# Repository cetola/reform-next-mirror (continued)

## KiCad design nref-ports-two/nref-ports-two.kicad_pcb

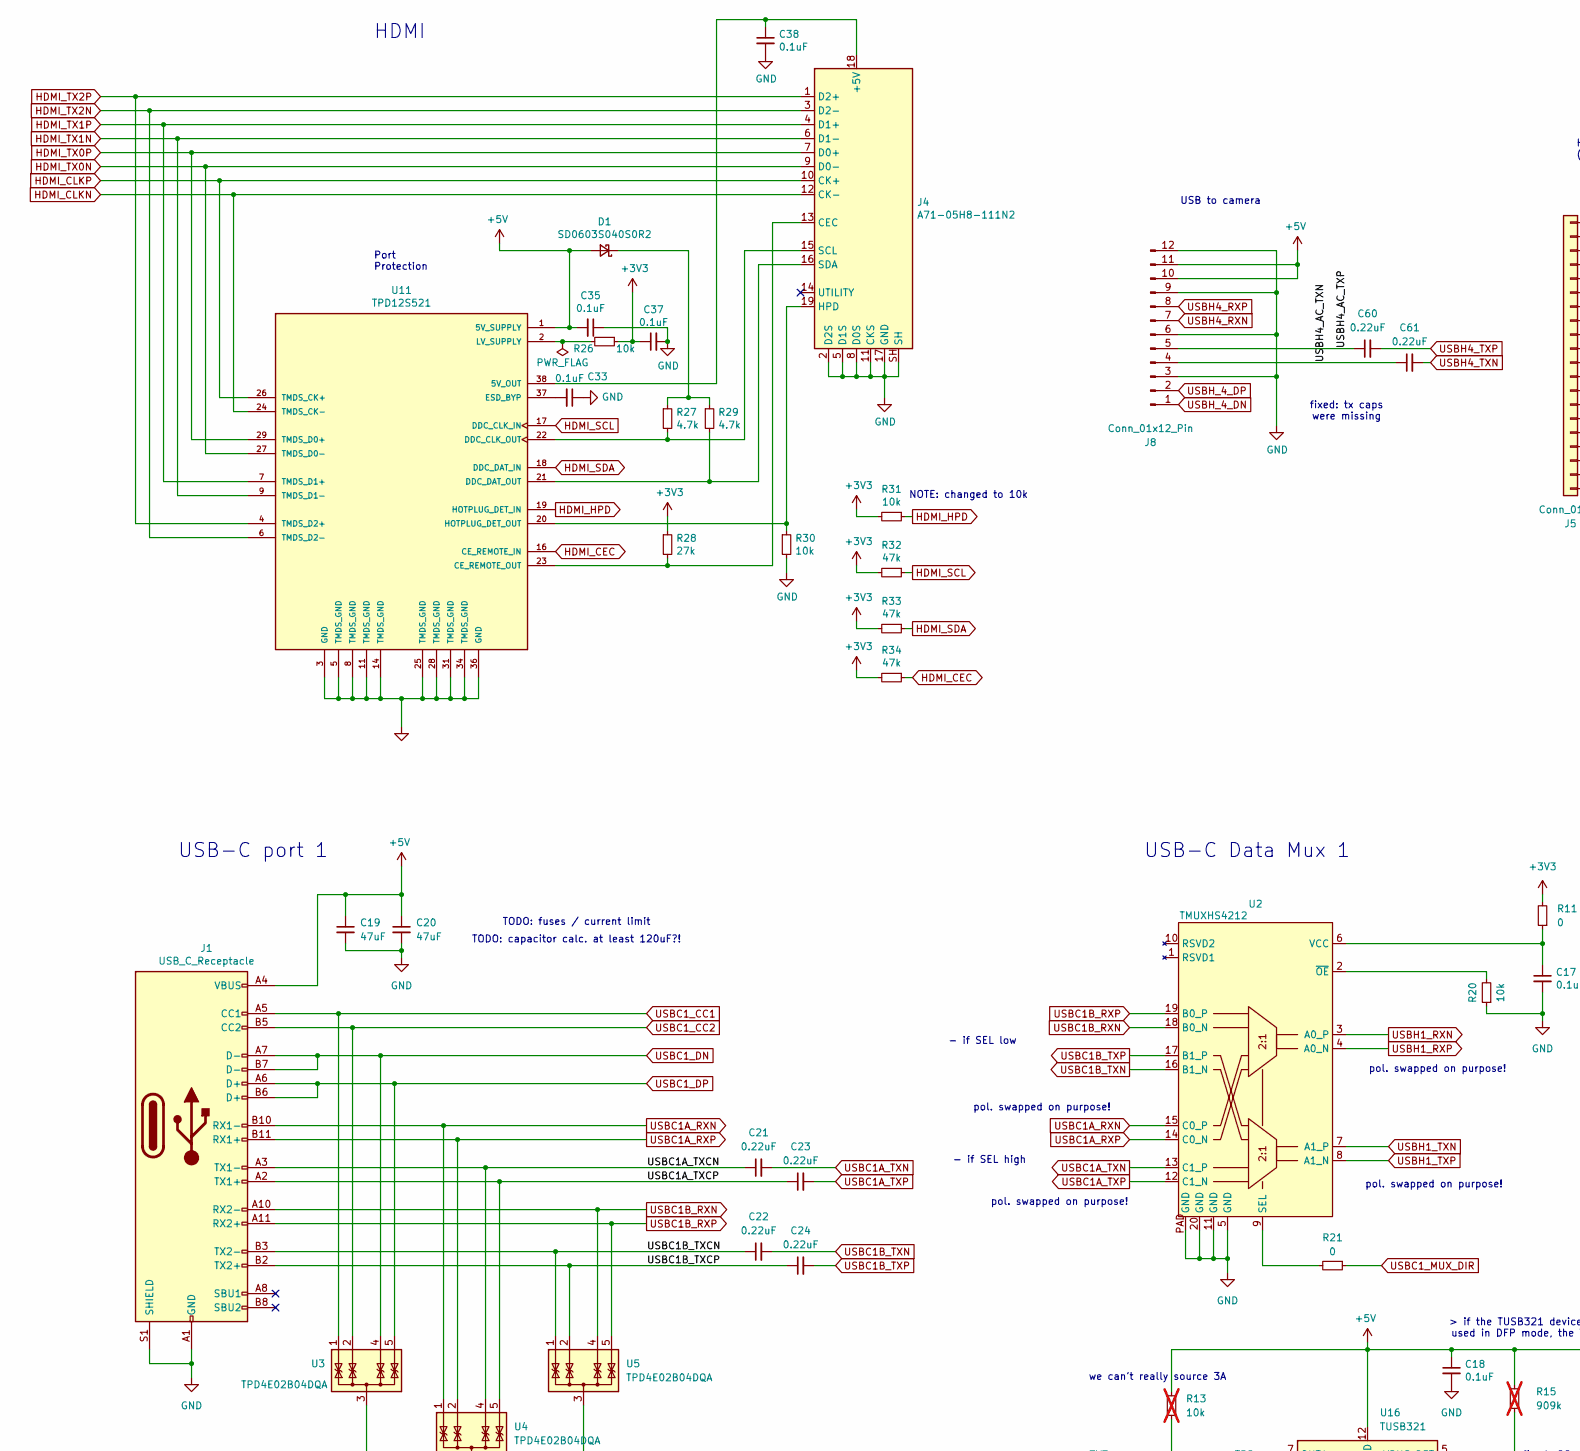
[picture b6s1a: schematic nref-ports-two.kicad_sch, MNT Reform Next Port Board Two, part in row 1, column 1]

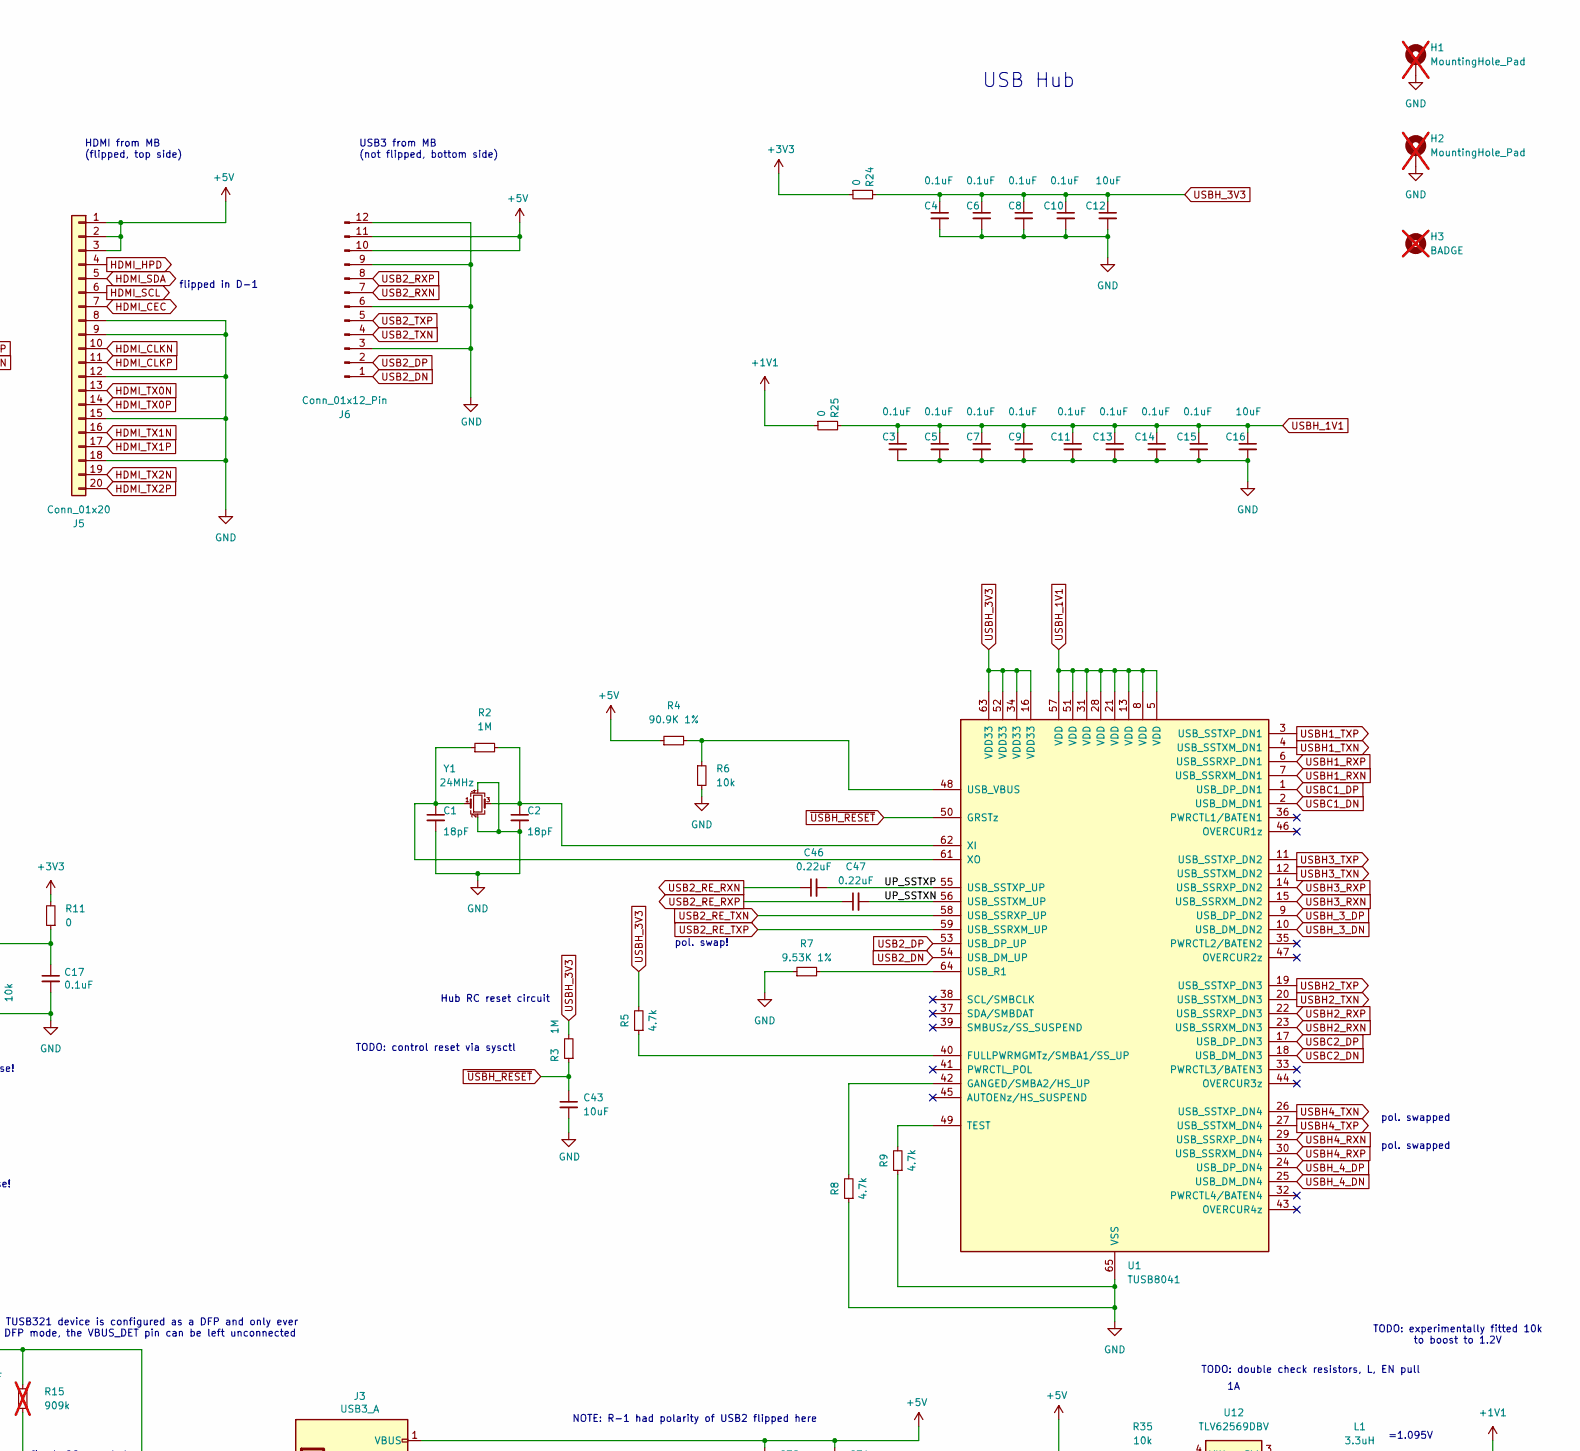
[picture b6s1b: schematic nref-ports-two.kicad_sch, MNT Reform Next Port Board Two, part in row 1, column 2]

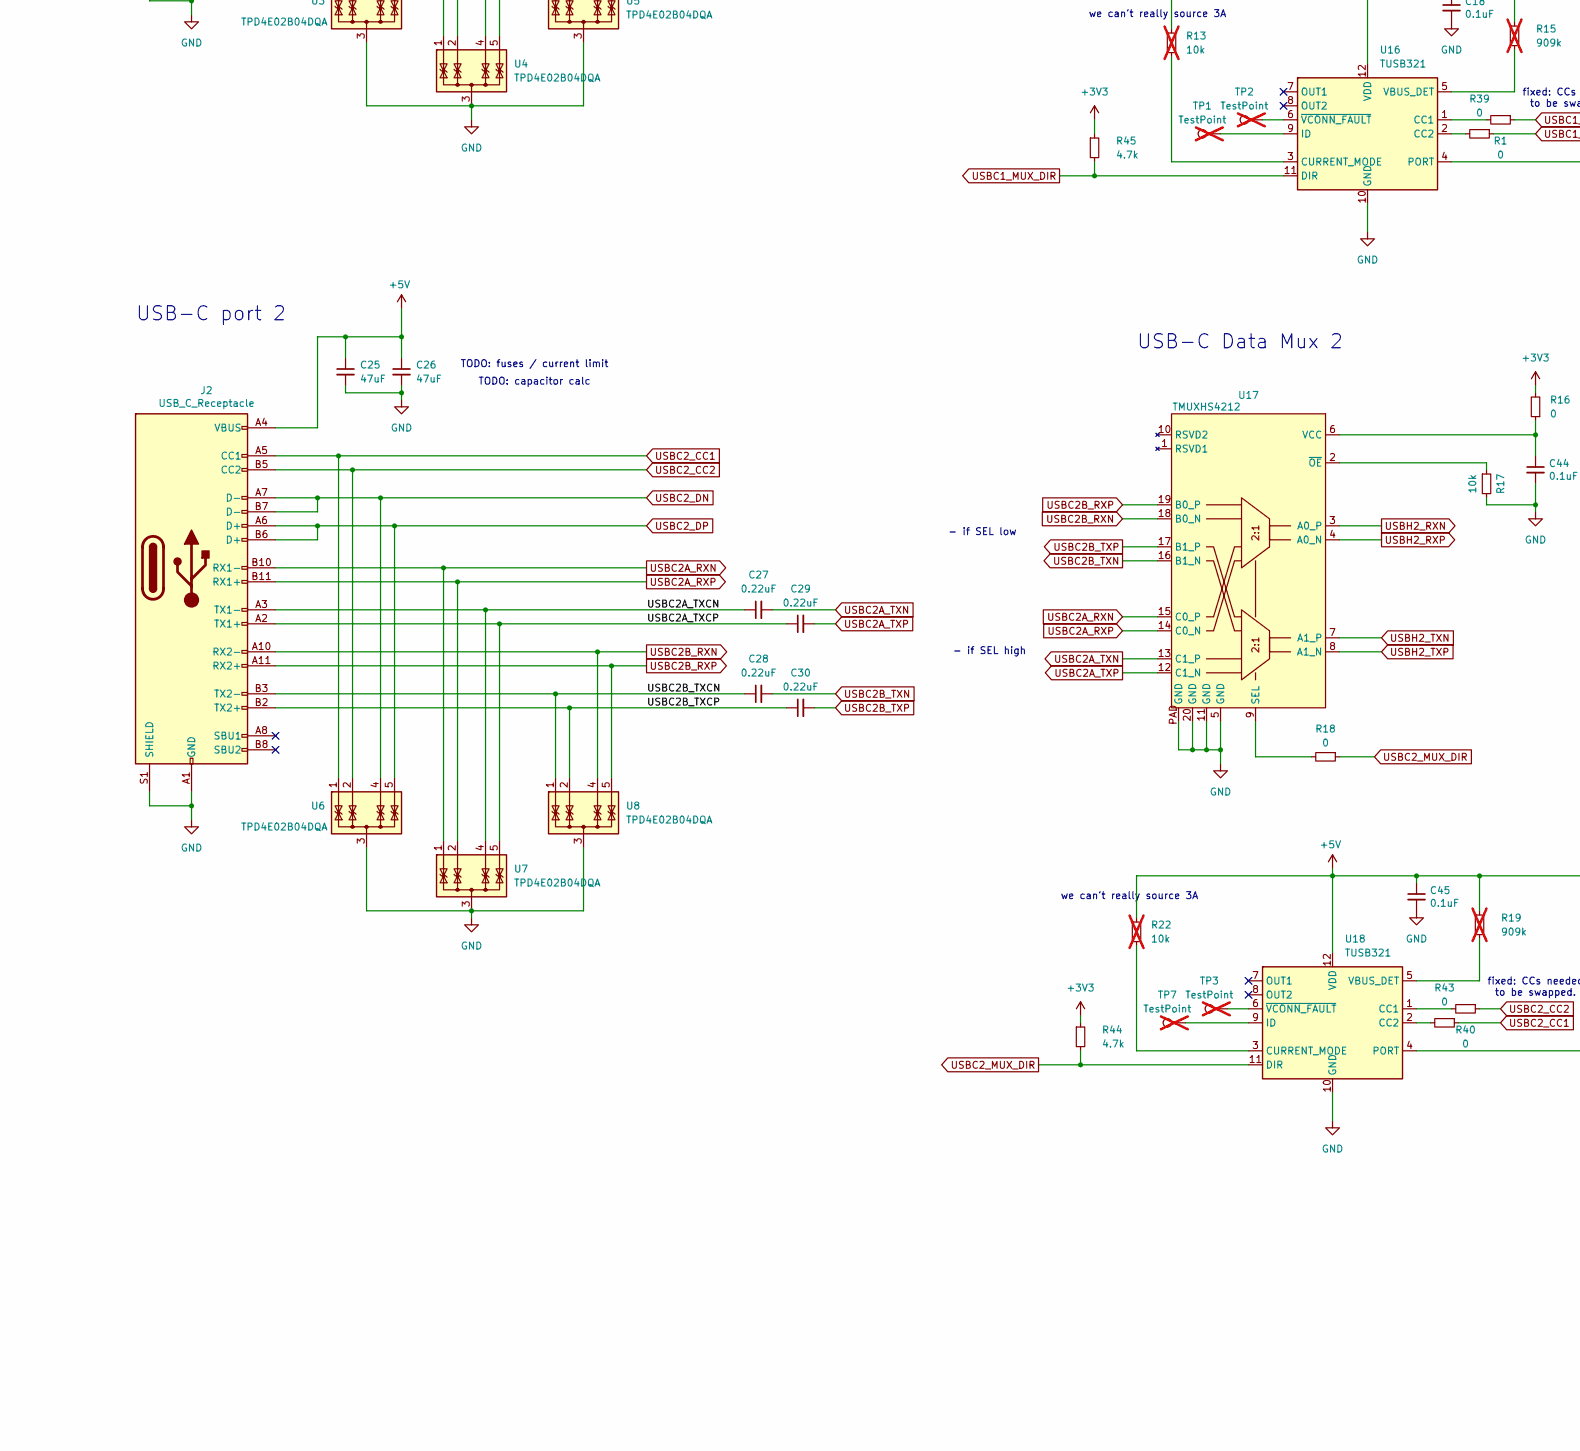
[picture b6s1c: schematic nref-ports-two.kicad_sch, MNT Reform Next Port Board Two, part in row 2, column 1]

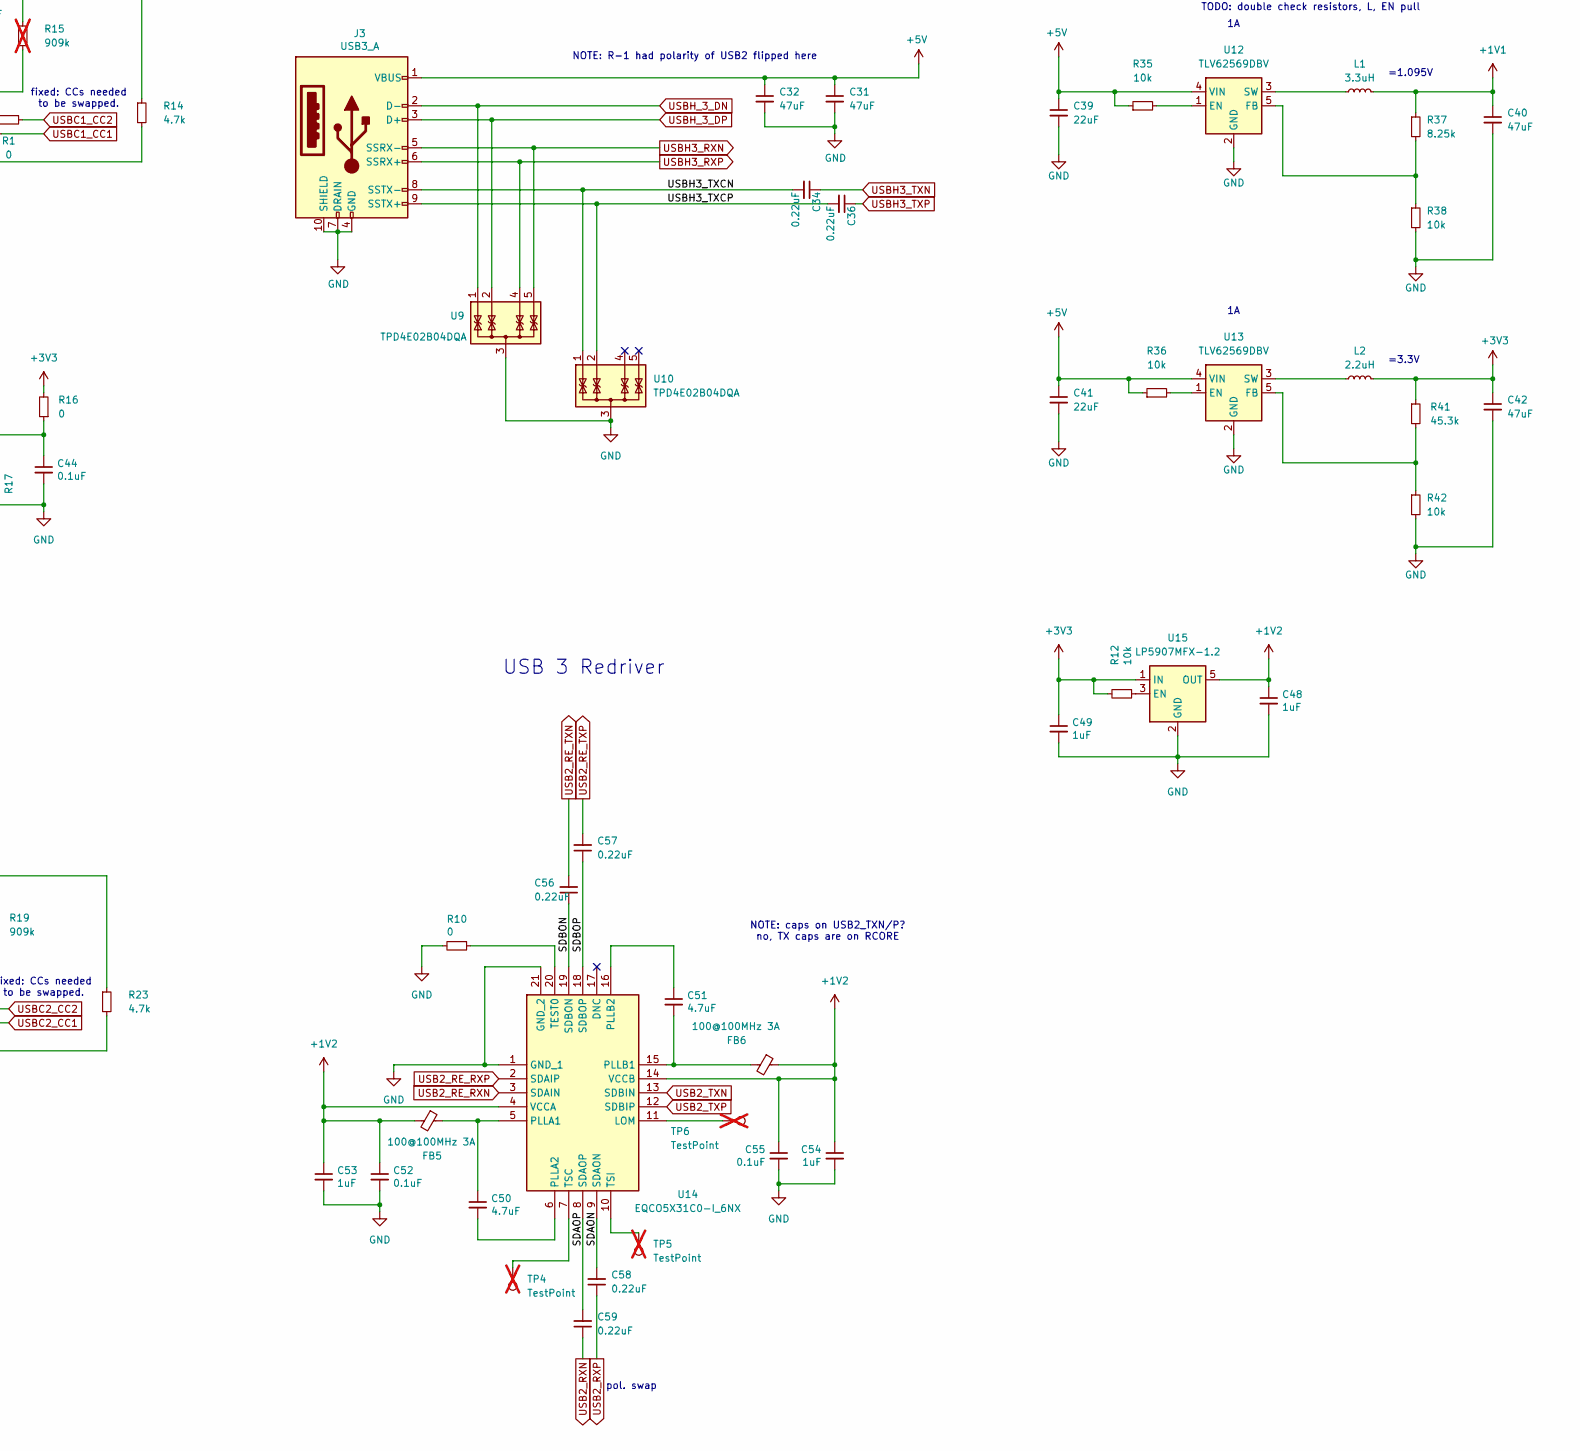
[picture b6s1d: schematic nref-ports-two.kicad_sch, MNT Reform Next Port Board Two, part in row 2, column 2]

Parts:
C1, C2: 18pF; C_0402_1005Metric; LCSC C1549
C3, C4, C5, C6, C7, C8, C9, C10, C11, C13, C14, C15, C17, C18, C33, C35, C37, C38, C44, C45, C52, C55: 0.1uF; C_0402_1005Metric; LCSC C1525
C12, C16, C43: 10uF; C_0603_1608Metric; LCSC C96446
C19, C20, C25, C26, C31, C32, C40, C42: 47uF; C_1206_3216Metric; LCSC C96123
C21, C22, C23, C24, C27, C28, C29, C30, C34, C36, C46, C47, C56, C57, C58, C59, C60, C61: 0.22uF; C_0402_1005Metric; LCSC C16772
C39, C41: 22uF; C_0603_1608Metric; LCSC C59461
C48, C49, C53, C54: 1uF; C_0402_1005Metric; LCSC C52923
C50, C51: 4.7uF; C_0402_1005Metric; LCSC C23733
D1: SD0603S040S0R2; D_0603_1608Metric; LCSC C143772
FB5, FB6: 100@100MHz 3A; L_0402_1005Metric; LCSC C124089
H1, H2: MountingHole_Pad; MountingHole_2.2mm_M2_Pad; not fitted
H3: BADGE; nref-ports-two-badge; not fitted
J1, J2: USB_C_Receptacle; USB_C_Receptacle_Molex_105450-0101; LCSC C134092
J3: USB3_A; USB-A-SMD_HC-USB3.0-C225-P; LCSC C7501855
J4: A71-05H8-111N2; HDMI-TH_A71-05H8-111N2; LCSC C2880638
J5: Conn_01x20; FPC-SMD_AFC07-S20ECC-00; LCSC C11090
J6, J8: Conn_01x12_Pin; Hirose_FH12-12S-0.5SH_1x12-1MP_P0.50mm_Horizontal; LCSC C262661
L1: 3.3uH; L_1210_3225Metric; LCSC C29780744
L2: 2.2uH; L_1210_3225Metric; LCSC C5832378
R1, R10, R11, R16, R18, R21, R24, R25, R39, R40, R43: 0; R_0402_1005Metric; LCSC C17168
R2, R3: 1M; R_0402_1005Metric; LCSC C26083
R4: 90.9K 1%; R_0402_1005Metric; LCSC C163452
R5, R8, R9, R14, R23, R27, R29, R44, R45: 4.7k; R_0402_1005Metric; LCSC C25900
R6, R12, R17, R20, R26, R30, R31, R35, R36, R38, R42: 10k; R_0402_1005Metric; LCSC C25744
R7: 9.53K 1%; R_0402_1005Metric; LCSC C96273
R13, R22: 10k; R_0402_1005Metric; LCSC C25744; not fitted
R15, R19: 909k; R_0402_1005Metric; LCSC C25799; not fitted
R28: 27k; R_0402_1005Metric; LCSC C25771
R32, R33, R34: 47k; R_0402_1005Metric; LCSC C25792
R37: 8.25k; R_0402_1005Metric; LCSC C5126132
R41: 45.3k; R_0402_1005Metric; LCSC C2933099
TP1, TP2, TP3, TP4, TP5, TP6, TP7: TestPoint; TestPoint_Pad_D1.0mm; not fitted
U1: TUSB8041; QFN-64-1EP_9x9mm_P0.5mm_EP6x6mm_ThermalVias; LCSC C544686
U2, U17: TMUXHS4212; Texas-VQFN20_2.5x4.5mm_RKS; LCSC C2869871
U3, U4, U5, U6, U7, U8, U9, U10: TPD4E02B04DQA; USON-10_2.5x1.0mm_P0.5mm; LCSC C2841426
U11: TPD12S521; TSSOP50P640X120-38N; LCSC C126920
U12, U13: TLV62569DBV; SOT-23-5; LCSC C141836
U14: EQCO5X31C0-I_6NX; QFN50P400X400X100-21N-D; LCSC C19729370
U15: LP5907MFX-1.2; SOT-23-5; LCSC C73478
U16, U18: TUSB321; Texas_X2QFN-12_1.6x1.6mm_P0.4mm; LCSC C2674046
Y1: 24MHz; Crystal_SMD_Abracon_ABM8G-4Pin_3.2x2.5mm; LCSC C91744

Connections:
+1V1: C40.1, L1.2, R25.1, R37.1
+1V2: C48.1, C52.1, C53.1, C54.1, C55.1, FB5.2, FB6.1, U14.4 (VCCA), U14.14 (VCCB), U15.5 (OUT)
+3V3: C37.1, C42.1, C49.1, L2.2, R11.2, R12.2, R16.2, R24.1, R26.1, R28.1, R31.2, R32.2, R33.2, R34.2, R41.1, R44.1, R45.1, U15.1 (IN)
+5V: C18.1, C19.1, C20.1, C25.1, C26.1, C31.1, C32.1, C35.2, C39.1, C41.1, C45.1, D1.2 (A), J1.A4 (VBUS), J1.A9 (VBUS), J1.B4 (VBUS), J1.B9 (VBUS), J2.A4 (VBUS), J2.A9 (VBUS), J2.B4 (VBUS), J2.B9 (VBUS), J3.1 (VBUS), J5.1, J5.2, J5.3, J6.10, J6.11, J8.10, J8.11, R4.1, R13.1, R14.1, R15.1, R19.1, R22.1, R23.1, R35.1, R36.1, U11.1 (5V_SUPPLY), U12.4 (VIN), U13.4 (VIN), U16.12 (VDD), U18.12 (VDD)
/SDAON: C58.2, U14.9 (SDAON)
/SDAOP: C59.2, U14.8 (SDAOP)
/SDBON: C56.1, U14.19 (SDBON)
/SDBOP: C57.1, U14.18 (SDBOP)
/UP_SSTXN: C47.2, U1.56 (USB_SSTXM_UP)
/UP_SSTXP: C46.2, U1.55 (USB_SSTXP_UP)
/USBC1A_TXCN: C21.1, J1.A3 (TX1-), U4.4 (IO3), U4.7 (IO3)
/USBC1A_TXCP: C23.1, J1.A2 (TX1+), U4.5 (IO4), U4.6 (IO4)
/USBC1B_TXCN: C22.1, J1.B3 (TX2-), U5.1 (IO1), U5.10 (IO1)
/USBC1B_TXCP: C24.1, J1.B2 (TX2+), U5.2 (IO2), U5.9 (IO2)
/USBC2A_TXCN: C27.1, J2.A3 (TX1-), U7.4 (IO3), U7.7 (IO3)
/USBC2A_TXCP: C29.1, J2.A2 (TX1+), U7.5 (IO4), U7.6 (IO4)
/USBC2B_TXCN: C28.1, J2.B3 (TX2-), U8.1 (IO1), U8.10 (IO1)
/USBC2B_TXCP: C30.1, J2.B2 (TX2+), U8.2 (IO2), U8.9 (IO2)
/USBH3_TXCN: C34.2, J3.8 (SSTX-), U10.1 (IO1), U10.10 (IO1)
/USBH3_TXCP: C36.2, J3.9 (SSTX+), U10.2 (IO2), U10.9 (IO2)
/USBH4_AC_TXN: C61.1, J8.4
/USBH4_AC_TXP: C60.1, J8.5
GND: C1.2, C2.2, C3.2, C4.2, C5.2, C6.2, C7.2, C8.2, C9.2, C10.2, C11.2, C12.2, C13.2, C14.2, C15.2, C16.2, C17.2, C18.2, C19.2, C20.2, C25.2, C26.2, C31.2, C32.2, C33.1, C35.1, C37.2, C38.2, C39.2, C40.2, C41.2, C42.2, C43.2, C44.2, C45.2, C48.2, C49.2, C52.2, C53.2, C54.2, C55.2, H1.1 (1_1), H2.1 (1_1), J1.A1 (GND), J1.A12 (GND), J1.B1 (GND), J1.B12 (GND), J1.S1 (SHIELD), J2.A1 (GND), J2.A12 (GND), J2.B1 (GND), J2.B12 (GND), J2.S1 (SHIELD), J3.4 (GND), J3.7 (DRAIN), J3.10 (SHIELD), J4.2 (D2S), J4.5 (D1S), J4.8 (D0S), J4.11 (CKS), J4.17 (GND), J4.SH, J5.8, J5.9, J5.12, J5.15, J5.18, J6.3, J6.6, J6.9, J6.12, J8.3, J8.6, J8.9, J8.12, R6.2, R7.1, R8.1, R9.1, R10.2, R17.2, R20.1, R30.2, R38.2, R42.2, U1.65 (VSS), U2.5 (GND), U2.11 (GND), U2.20 (GND), U2.PAD (GND), U3.3 (G), U3.8 (G), U4.3 (G), U4.8 (G), U5.3 (G), U5.8 (G), U6.3 (G), U6.8 (G), U7.3 (G), U7.8 (G), U8.3 (G), U8.8 (G), U9.3 (G), U9.8 (G), U10.3 (G), U10.8 (G), U11.3 (GND), U11.5 (TMDS_GND), U11.8 (TMDS_GND), U11.11 (TMDS_GND), U11.14 (TMDS_GND), U11.25 (TMDS_GND), U11.28 (TMDS_GND), U11.31 (TMDS_GND), U11.34 (TMDS_GND), U11.36 (GND), U12.2 (GND), U13.2 (GND), U14.1 (GND_1), U14.21 (GND_2), U15.2 (GND), U16.10 (GND), U17.5 (GND), U17.11 (GND), U17.20 (GND), U17.PAD (GND), U18.10 (GND), Y1.2, Y1.4
HDMI_CEC: J5.7, R34.1, U11.16 (CE_REMOTE_IN)
HDMI_CLKN: J4.12 (CK-), J5.10, U11.15 (TMDS_CK-), U11.24 (TMDS_CK-)
HDMI_CLKP: J4.10 (CK+), J5.11, U11.13 (TMDS_CK+), U11.26 (TMDS_CK+)
HDMI_HPD: J5.4, R31.1, U11.19 (HOTPLUG_DET_IN)
HDMI_SCL: J5.6, R32.1, U11.17 (DDC_CLK_IN)
HDMI_SDA: J5.5, R33.1, U11.18 (DDC_DAT_IN)
HDMI_TX0N: J4.9 (D0-), J5.13, U11.12 (TMDS_D0-), U11.27 (TMDS_D0-)
HDMI_TX0P: J4.7 (D0+), J5.14, U11.10 (TMDS_D0+), U11.29 (TMDS_D0+)
HDMI_TX1N: J4.6 (D1-), J5.16, U11.9 (TMDS_D1-), U11.30 (TMDS_D1-)
HDMI_TX1P: J4.4 (D1+), J5.17, U11.7 (TMDS_D1+), U11.32 (TMDS_D1+)
HDMI_TX2N: J4.3 (D2-), J5.19, U11.6 (TMDS_D2-), U11.33 (TMDS_D2-)
HDMI_TX2P: J4.1 (D2+), J5.20, U11.4 (TMDS_D2+), U11.35 (TMDS_D2+)
unnamed: D1.1 (K), R27.1, R29.1
unnamed: C38.1, J4.18 (+5V), U11.38 (5V_OUT)
unnamed: J4.13 (CEC), R28.2, U11.23 (CE_REMOTE_OUT)
unnamed: J4.19 (HPD), R30.1, U11.20 (HOTPLUG_DET_OUT)
unnamed: J4.15 (SCL), R27.2, U11.22 (DDC_CLK_OUT)
unnamed: J4.16 (SDA), R29.2, U11.21 (DDC_DAT_OUT)
unnamed: R5.1, U1.40 (FULLPWRMGMTz/SMBA1/SS_UP)
unnamed: R8.2, U1.42 (GANGED/SMBA2/HS_UP)
unnamed: R9.2, U1.49 (TEST)
unnamed: R7.2, U1.64 (USB_R1)
unnamed: R4.2, R6.1, U1.48 (USB_VBUS)
unnamed: C2.1, R2.2, U1.62 (XI), Y1.3
unnamed: C1.1, R2.1, U1.61 (XO), Y1.1
unnamed: R21.2, U2.9 (SEL)
unnamed: C17.1, R11.1, U2.6 (VCC)
unnamed: R20.2, U2.2 (~OE)
unnamed: C33.2, U11.37 (ESD_BYP)
unnamed: R26.2, U11.2 (LV_SUPPLY)
unnamed: R35.2, U12.1 (EN)
unnamed: R37.2, R38.1, U12.5 (FB)
unnamed: L1.1, U12.3 (SW)
unnamed: R36.2, U13.1 (EN)
unnamed: R41.2, R42.1, U13.5 (FB)
unnamed: L2.1, U13.3 (SW)
unnamed: TP6.1 (1_1), U14.11 (LOM)
unnamed: C50.1, FB5.1, U14.5 (PLLA1)
unnamed: C50.2, U14.6 (PLLA2)
unnamed: C51.2, FB6.2, U14.15 (PLLB1)
unnamed: C51.1, U14.16 (PLLB2)
unnamed: R10.1, U14.20 (TEST0)
unnamed: TP4.1 (1_1), U14.7 (TSC)
unnamed: TP5.1 (1_1), U14.10 (TSI)
unnamed: R12.1, U15.3 (EN)
unnamed: R1.2, U16.1 (CC1)
unnamed: R39.2, U16.2 (CC2)
unnamed: R13.2, U16.3 (CURRENT_MODE)
unnamed: TP1.1 (1_1), U16.9 (ID)
unnamed: R14.2, U16.4 (PORT)
unnamed: R15.2, U16.5 (VBUS_DET)
unnamed: TP2.1 (1_1), U16.6 (~VCONN_FAULT)
unnamed: R18.2, U17.9 (SEL)
unnamed: C44.1, R16.1, U17.6 (VCC)
unnamed: R17.1, U17.2 (~OE)
unnamed: R40.2, U18.1 (CC1)
unnamed: R43.2, U18.2 (CC2)
unnamed: R22.2, U18.3 (CURRENT_MODE)
unnamed: TP7.1 (1_1), U18.9 (ID)
unnamed: R23.2, U18.4 (PORT)
unnamed: R19.2, U18.5 (VBUS_DET)
unnamed: TP3.1 (1_1), U18.6 (~VCONN_FAULT)
USB2_DN: J6.1, U1.54 (USB_DM_UP)
USB2_DP: J6.2, U1.53 (USB_DP_UP)
USB2_RE_RXN: C46.1, U14.3 (SDAIN)
USB2_RE_RXP: C47.1, U14.2 (SDAIP)
USB2_RE_TXN: C56.2, U1.58 (USB_SSRXP_UP)
USB2_RE_TXP: C57.2, U1.59 (USB_SSRXM_UP)
USB2_RXN: C59.1, J6.7
USB2_RXP: C58.1, J6.8
USB2_TXN: J6.4, U14.13 (SDBIN)
USB2_TXP: J6.5, U14.12 (SDBIP)
USBC1A_RXN: J1.B10 (RX1-), U2.15 (C0_P), U4.1 (IO1), U4.10 (IO1)
USBC1A_RXP: J1.B11 (RX1+), U2.14 (C0_N), U4.2 (IO2), U4.9 (IO2)
USBC1A_TXN: C21.2, U2.13 (C1_P)
USBC1A_TXP: C23.2, U2.12 (C1_N)
USBC1B_RXN: J1.A10 (RX2-), U2.18 (B0_N), U5.4 (IO3), U5.7 (IO3)
USBC1B_RXP: J1.A11 (RX2+), U2.19 (B0_P), U5.5 (IO4), U5.6 (IO4)
USBC1B_TXN: C22.2, U2.16 (B1_N)
USBC1B_TXP: C24.2, U2.17 (B1_P)
USBC1_CC1: J1.A5 (CC1), R39.1, U3.1 (IO1), U3.10 (IO1)
USBC1_CC2: J1.B5 (CC2), R1.1, U3.2 (IO2), U3.9 (IO2)
USBC1_DN: J1.A7 (D-), J1.B7 (D-), U1.2 (USB_DM_DN1), U3.4 (IO3), U3.7 (IO3)
USBC1_DP: J1.A6 (D+), J1.B6 (D+), U1.1 (USB_DP_DN1), U3.5 (IO4), U3.6 (IO4)
USBC1_MUX_DIR: R21.1, R45.2, U16.11 (DIR)
USBC2A_RXN: J2.B10 (RX1-), U7.1 (IO1), U7.10 (IO1), U17.15 (C0_P)
USBC2A_RXP: J2.B11 (RX1+), U7.2 (IO2), U7.9 (IO2), U17.14 (C0_N)
USBC2A_TXN: C27.2, U17.13 (C1_P)
USBC2A_TXP: C29.2, U17.12 (C1_N)
USBC2B_RXN: J2.A10 (RX2-), U8.4 (IO3), U8.7 (IO3), U17.18 (B0_N)
USBC2B_RXP: J2.A11 (RX2+), U8.5 (IO4), U8.6 (IO4), U17.19 (B0_P)
USBC2B_TXN: C28.2, U17.16 (B1_N)
USBC2B_TXP: C30.2, U17.17 (B1_P)
USBC2_CC1: J2.A5 (CC1), R43.1, U6.1 (IO1), U6.10 (IO1)
USBC2_CC2: J2.B5 (CC2), R40.1, U6.2 (IO2), U6.9 (IO2)
USBC2_DN: J2.A7 (D-), J2.B7 (D-), U1.18 (USB_DM_DN3), U6.4 (IO3), U6.7 (IO3)
USBC2_DP: J2.A6 (D+), J2.B6 (D+), U1.17 (USB_DP_DN3), U6.5 (IO4), U6.6 (IO4)
USBC2_MUX_DIR: R18.1, R44.2, U18.11 (DIR)
USBH1_RXN: U1.7 (USB_SSRXM_DN1), U2.3 (A0_P)
USBH1_RXP: U1.6 (USB_SSRXP_DN1), U2.4 (A0_N)
USBH1_TXN: U1.4 (USB_SSTXM_DN1), U2.7 (A1_P)
USBH1_TXP: U1.3 (USB_SSTXP_DN1), U2.8 (A1_N)
USBH2_RXN: U1.23 (USB_SSRXM_DN3), U17.3 (A0_P)
USBH2_RXP: U1.22 (USB_SSRXP_DN3), U17.4 (A0_N)
USBH2_TXN: U1.20 (USB_SSTXM_DN3), U17.7 (A1_P)
USBH2_TXP: U1.19 (USB_SSTXP_DN3), U17.8 (A1_N)
USBH3_RXN: J3.5 (SSRX-), U1.15 (USB_SSRXM_DN2), U9.5 (IO4), U9.6 (IO4)
USBH3_RXP: J3.6 (SSRX+), U1.14 (USB_SSRXP_DN2), U9.4 (IO3), U9.7 (IO3)
USBH3_TXN: C34.1, U1.12 (USB_SSTXM_DN2)
USBH3_TXP: C36.1, U1.11 (USB_SSTXP_DN2)
USBH4_RXN: J8.7, U1.29 (USB_SSRXP_DN4)
USBH4_RXP: J8.8, U1.30 (USB_SSRXM_DN4)
USBH4_TXN: C61.2, U1.26 (USB_SSTXP_DN4)
USBH4_TXP: C60.2, U1.27 (USB_SSTXM_DN4)
USBH_1V1: C3.1, C5.1, C7.1, C9.1, C11.1, C13.1, C14.1, C15.1, C16.1, R25.2, U1.5 (VDD), U1.8 (VDD), U1.13 (VDD), U1.21 (VDD), U1.28 (VDD), U1.31 (VDD), U1.51 (VDD), U1.57 (VDD)
USBH_3V3: C4.1, C6.1, C8.1, C10.1, C12.1, R3.2, R5.2, R24.2, U1.16 (VDD33), U1.34 (VDD33), U1.52 (VDD33), U1.63 (VDD33)
USBH_3_DN: J3.2 (D-), U1.10 (USB_DM_DN2), U9.1 (IO1), U9.10 (IO1)
USBH_3_DP: J3.3 (D+), U1.9 (USB_DP_DN2), U9.2 (IO2), U9.9 (IO2)
USBH_4_DN: J8.1, U1.25 (USB_DM_DN4)
USBH_4_DP: J8.2, U1.24 (USB_DP_DN4)
~USBH_RESET: C43.1, R3.1, U1.50 (GRSTz)

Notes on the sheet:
TODO: fuses / current limit
USB3 from MB (not flipped, bottom side)
NOTE: caps on USB2_TXN/P? no, TX caps are on RCORE
- if SEL low
NOTE: changed to 10k
Hub RC reset circuit
pol. swapped
=1.095V
USB-C Data Mux 2
> if the TUSB321 device is configured as a DFP and only ever used in DFP mode, the VBUS_DET pin can be left unconnected
- if SEL high
fixed: CCs needed to be swapped.
=3.3V
pol. swapped on purpose!
we can't really source 3A
flipped in D-1
NOTE: R-1 had polarity of USB2 flipped here
pol. swap!
USB-C port 1
USB 3 Redriver
HDMI from MB (flipped, top side)
TODO: double check resistors, L, EN pull
USB-C Data Mux 1
TODO: control reset via sysctl
fixed: tx caps were missing
USB to camera
pol. swap
TODO: experimentally fitted 10k to boost to 1.2V
HDMI
USB-C port 2
Port Protection
USB Hub
TODO: capacitor calc. at least 120uF?!
TODO: capacitor calc

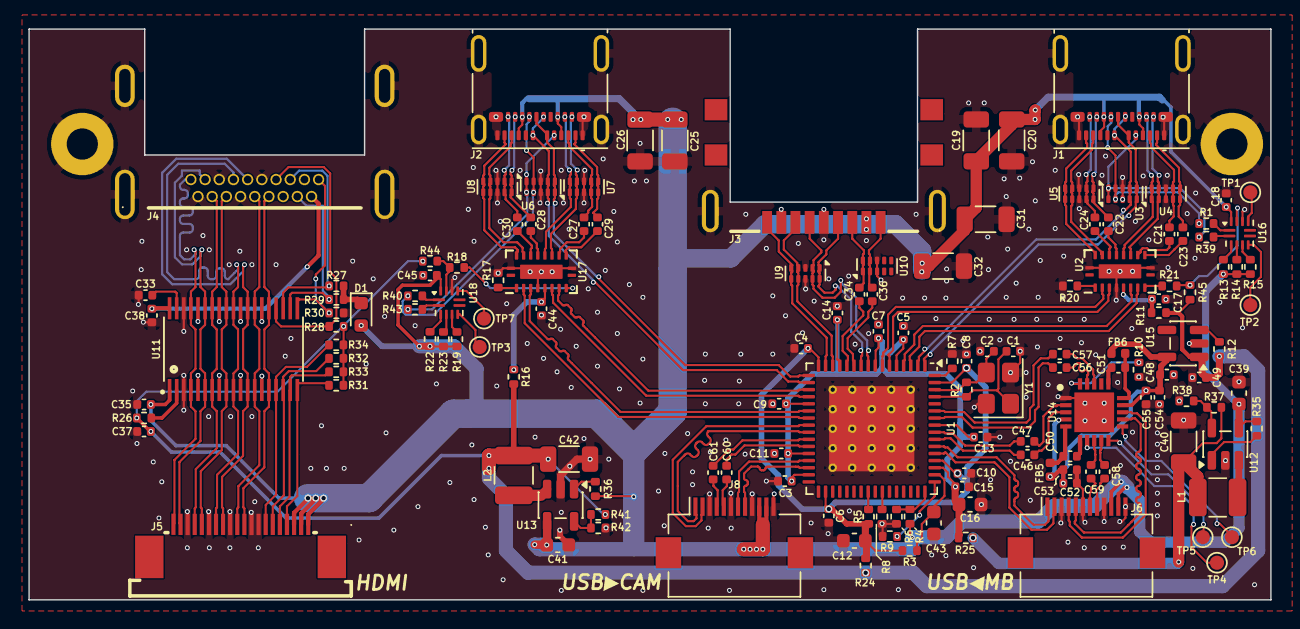
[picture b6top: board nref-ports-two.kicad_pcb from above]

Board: 4 copper layers, 87.5 x 40.2 mm, 147 parts (1 on the bottom side), 144 nets.

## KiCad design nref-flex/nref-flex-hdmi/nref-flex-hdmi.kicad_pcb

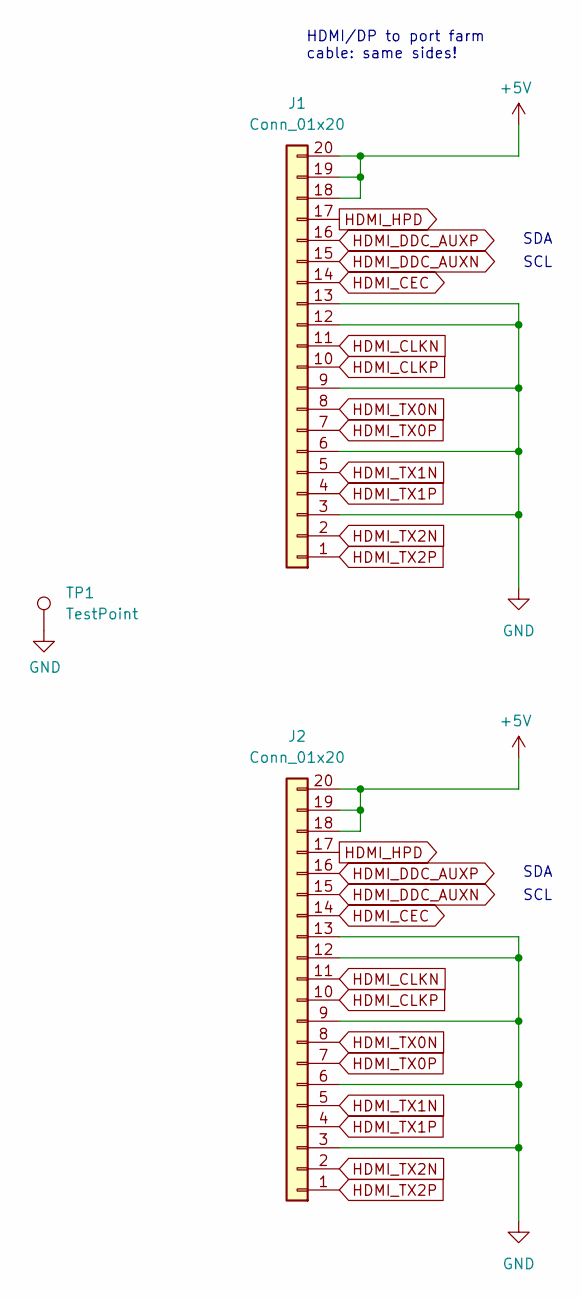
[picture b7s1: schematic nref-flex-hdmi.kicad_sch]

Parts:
J1, J2: Conn_01x20; Hirose_FH12-20S-0.5SH_1x20-1MP_P0.50mm_Horizontal
TP1: TestPoint; TestPoint_Pad_D1.0mm

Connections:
+5V: J1.18, J1.19, J1.20, J2.18, J2.19, J2.20
GND: J1.3, J1.6, J1.9, J1.12, J1.13, J2.3, J2.6, J2.9, J2.12, J2.13, TP1.1
HDMI_CEC: J1.14, J2.14
HDMI_CLKN: J1.11, J2.11
HDMI_CLKP: J1.10, J2.10
HDMI_DDC_AUXN: J1.15, J2.15
HDMI_DDC_AUXP: J1.16, J2.16
HDMI_HPD: J1.17, J2.17
HDMI_TX0N: J1.8, J2.8
HDMI_TX0P: J1.7, J2.7
HDMI_TX1N: J1.5, J2.5
HDMI_TX1P: J1.4, J2.4
HDMI_TX2N: J1.2, J2.2
HDMI_TX2P: J1.1, J2.1

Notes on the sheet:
SDA
SCL
HDMI/DP to port farm cable: same sides!

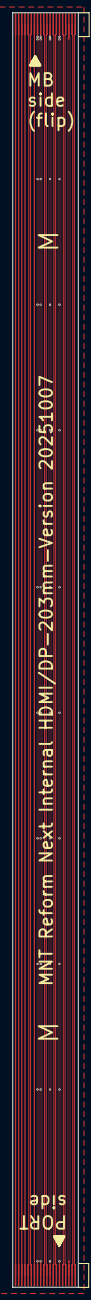
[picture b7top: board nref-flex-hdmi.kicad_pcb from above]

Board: 2 copper layers, 10.5 x 203.0 mm, 3 parts (1 on the bottom side), 14 nets.
